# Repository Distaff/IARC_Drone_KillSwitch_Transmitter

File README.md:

# Killswitch for IARC Hat for CMDB
## PCB Design

Board layout:

3D render:

## Usage
- Broadcast killing signal for drones using IARC CMDB hat or other LoRa-based killswitch
- Serve as LoRa packet grabber (by connecting to PC through UART

Board can be powered either from 2x 18650 cells or directly from USB-C (if host provides enough power).
No built-in undervoltage protection circuit is present, except for a warning LED.

## Authors
- Szymon Konopka (PCB Design)
- Piotr Kądziela (schematic design and PCB review)

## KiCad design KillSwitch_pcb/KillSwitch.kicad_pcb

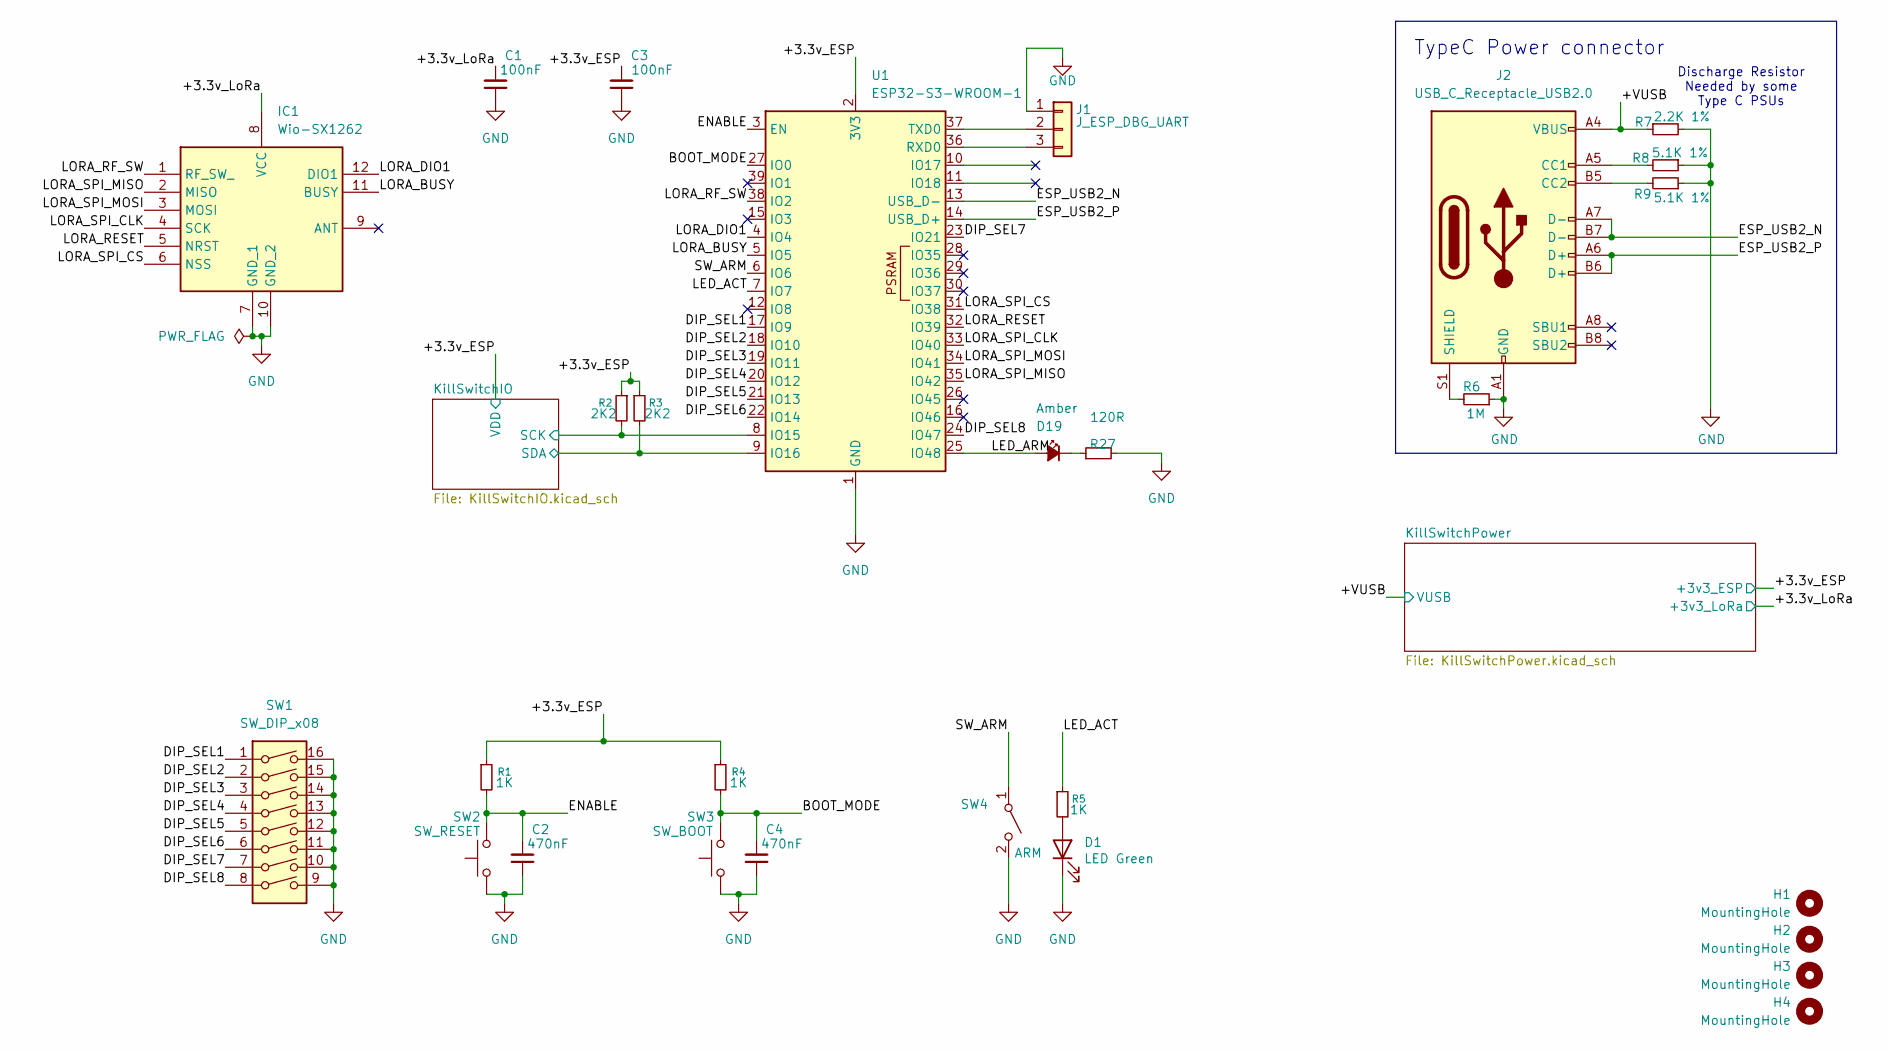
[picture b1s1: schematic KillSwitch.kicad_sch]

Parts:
C1, C3: 100nF; C_0805_2012Metric_Pad1.18x1.45mm_HandSolder
C2, C4: 470nF; C_0805_2012Metric_Pad1.18x1.45mm_HandSolder
D1: LED Green; LED_0603_1608Metric; Part Description Green 572nm LED Indication - Discrete 2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
D19: Amber; LED_Rectangular_W5.0mm_H2.0mm
H1, H2, H3, H4: MountingHole; MountingHole_3.2mm_M3_DIN965
IC1: Wio-SX1262; Mouser Part Number 713-114993390
J1: J_ESP_DBG_UART; Molex_PicoBlade_53047-0310_1x03_P1.25mm_Vertical; Part Description Pin Header, Vertical, Signal, Wire-to-B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
J2: USB_C_Receptacle_USB2.0; USB_C_Receptacle_GCT_USB4105-xx-A_16P_TopMnt_Horizontal; Part Description USBC USB2 data and power connector
R1, R4, R5: 1K; R_0805_2012Metric_Pad1.20x1.40mm_HandSolder
R2, R3: 2K2; R_0805_2012Metric_Pad1.20x1.40mm_HandSolder
R6: 1M; R_0805_2012Metric_Pad1.20x1.40mm_HandSolder; Part Description Resistor 5.1K 1% 63mW
R7: 2.2K 1%; R_0805_2012Metric_Pad1.20x1.40mm_HandSolder; Part Description Resistor 2.2K 1% 63mW
R8, R9: 5.1K 1%; R_0805_2012Metric_Pad1.20x1.40mm_HandSolder; Part Description Resistor 5.1K 1% 63mW
R27: 120R; R_0805_2012Metric_Pad1.20x1.40mm_HandSolder
SW1: SW_DIP_x08; SW_DIP_SPSTx08_Slide_6.7x21.88mm_W8.61mm_P2.54mm_LowProfile
SW2: SW_RESET; SW_Push_1P1T_NO_CK_KMR2; Part Description Tactile Switch, KMR 2 Series, Top Actua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
SW3: SW_BOOT; SW_Push_1P1T_NO_CK_KMR2; Part Description Tactile Switch, KMR 2 Series, Top Actua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
SW4: ARM; SW_Toggle_Blue_wSlots
U1: ESP32-S3-WROOM-1; ESP32-S3-WROOM-1U

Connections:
/+3.3v_ESP: C3.2, R1.1, R2.1, R3.1, R4.1, U1.2 (3V3); also elsewhere on the board
/+3.3v_LoRa: C1.2, IC1.8 (VCC); also elsewhere on the board
/+VUSB: J2.A4 (VBUS), J2.A9 (VBUS), J2.B4 (VBUS), J2.B9 (VBUS), R7.1; also elsewhere on the board
/BOOT_MODE: C4.2, R4.2, SW3.2, U1.27 (IO0)
/DIP_SEL1: SW1.1, U1.17 (IO9)
/DIP_SEL2: SW1.2, U1.18 (IO10)
/DIP_SEL3: SW1.3, U1.19 (IO11)
/DIP_SEL4: SW1.4, U1.20 (IO12)
/DIP_SEL5: SW1.5, U1.21 (IO13)
/DIP_SEL6: SW1.6, U1.22 (IO14)
/DIP_SEL7: SW1.7, U1.23 (IO21)
/DIP_SEL8: SW1.8, U1.24 (IO47)
/ENABLE: C2.2, R1.2, SW2.2, U1.3 (EN)
/ESP_USB2_N: J2.A7 (D-), J2.B7 (D-), U1.13 (USB_D-)
/ESP_USB2_P: J2.A6 (D+), J2.B6 (D+), U1.14 (USB_D+)
/KillSwitchIO/SCK: R2.2, U1.8 (IO15); also elsewhere on the board
/KillSwitchIO/SDA: R3.2, U1.9 (IO16); also elsewhere on the board
/LED_ACT: R5.1, U1.7 (IO7)
/LED_ARM: D19.2 (A), U1.25 (IO48)
/LORA_BUSY: IC1.11 (BUSY), U1.5 (IO5)
/LORA_DIO1: IC1.12 (DIO1), U1.4 (IO4)
/LORA_RESET: IC1.5 (NRST), U1.32 (IO39)
/LORA_RF_SW: IC1.1 (RF_SW_), U1.38 (IO2)
/LORA_SPI_CLK: IC1.4 (SCK), U1.33 (IO40)
/LORA_SPI_CS: IC1.6 (NSS), U1.31 (IO38)
/LORA_SPI_MISO: IC1.2 (MISO), U1.35 (IO42)
/LORA_SPI_MOSI: IC1.3 (MOSI), U1.34 (IO41)
/SW_ARM: SW4.1 (A), U1.6 (IO6)
GND: C1.1, C2.1, C3.1, C4.1, D1.1 (K), IC1.7 (GND_1), IC1.10 (GND_2), J1.1, J2.A1 (GND), J2.A12 (GND), J2.B1 (GND), J2.B12 (GND), R6.1, R7.2, R8.1, R9.1, R27.2, SW1.9, SW1.10, SW1.11, SW1.12, SW1.13, SW1.14, SW1.15, SW1.16, SW2.1, SW3.1, SW4.2 (B), U1.1 (GND), U1.40 (GND), U1.41 (GND); also elsewhere on the board
unnamed: D1.2 (A), R5.2
unnamed: D19.1 (K), R27.1
unnamed: J1.2, U1.37 (TXD0)
unnamed: J1.3, U1.36 (RXD0)
unnamed: J2.A5 (CC1), R8.2
unnamed: J2.B5 (CC2), R9.2
unnamed: J2.S1 (SHIELD), R6.2

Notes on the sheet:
Discharge Resistor Needed by some Type C PSUs
TypeC Power connector

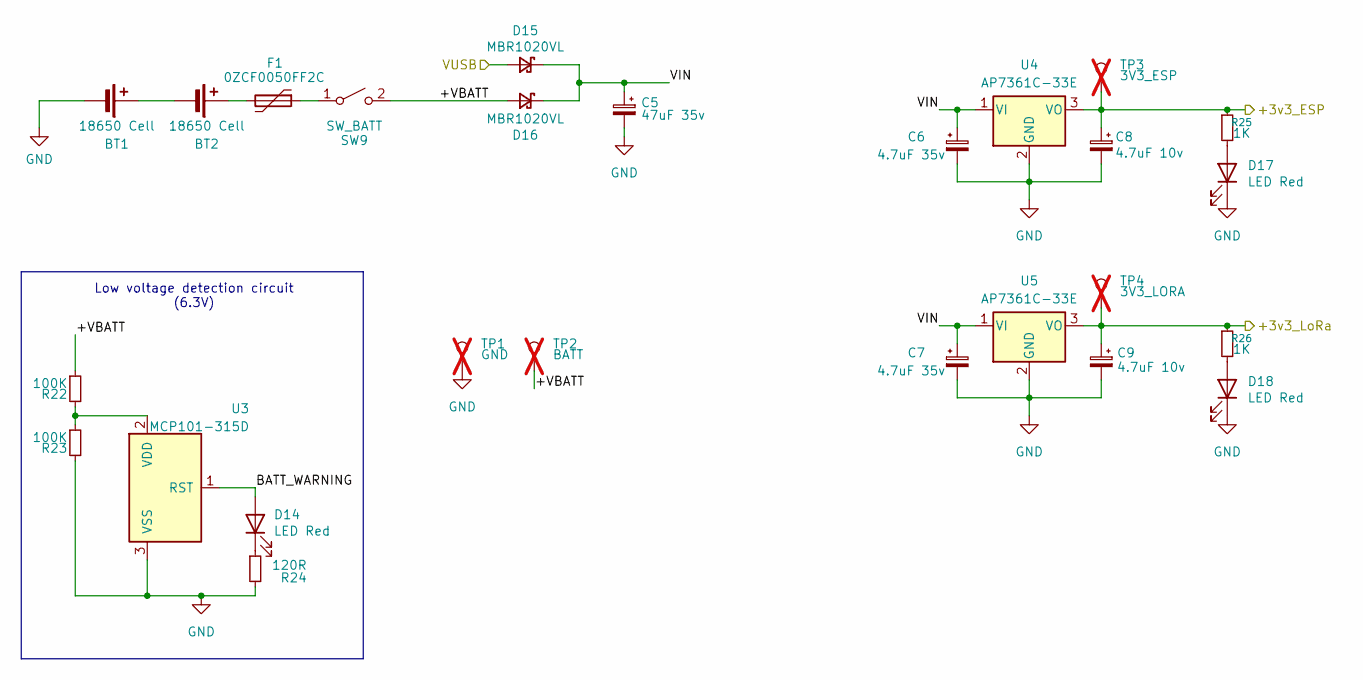
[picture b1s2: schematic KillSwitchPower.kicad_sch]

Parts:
BT1, BT2: 18650 Cell; BAT_BH-18650-PC
C5: 47uF 35v; CP_EIA-7343-31_Kemet-D_HandSolder
C6, C7: 4.7uF 35v; CP_EIA-3528-21_Kemet-B_HandSolder
C8, C9: 4.7uF 10v; CP_EIA-3216-18_Kemet-A_HandSolder
D14, D17, D18: LED Red; LED_0603_1608Metric; Part Description Red 620nm LED Indication - Discrete 2.2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
D15, D16: MBR1020VL; D_SOD-123F
F1: 0ZCF0050FF2C; Fuse_2920_7451Metric_Pad2.10x5.45mm_HandSolder
R22, R23: 100K; R_0805_2012Metric_Pad1.20x1.40mm_HandSolder
R24: 120R; R_Axial_DIN0204_L3.6mm_D1.6mm_P2.54mm_Vertical
R25, R26: 1K; R_0805_2012Metric_Pad1.20x1.40mm_HandSolder
SW9: SW_BATT; SL19121
TP1: GND; TestPoint_Pad_2.0x2.0mm; Part Description Test point; not fitted
TP2: BATT; TestPoint_Pad_2.0x2.0mm; Part Description Test point; not fitted
TP3: 3V3_ESP; TestPoint_Pad_2.0x2.0mm; Part Description Test point; not fitted
TP4: 3V3_LORA; TestPoint_Pad_2.0x2.0mm; Part Description Test point; not fitted
U3: MCP101-315D; SOT-23-3
U4, U5: AP7361C-33E; SOT-223-3_TabPin2; Part Description LDO, FIXED, 3.3V, 1A, -40 TO 85DEG C

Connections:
/+3.3v_ESP: C8.1, R25.1, TP3.1, U4.3 (VO); also elsewhere on the board
/+3.3v_LoRa: C9.1, R26.1, TP4.1, U5.3 (VO); also elsewhere on the board
/+VUSB: D15.2 (A); also elsewhere on the board
/KillSwitchPower/+VBATT: D16.2 (A), R22.1, SW9.2 (B), TP2.1
/KillSwitchPower/BATT_WARNING: D14.2 (A), U3.1 (RST)
/KillSwitchPower/VIN: C5.1, C6.1, C7.1, D15.1 (K), D16.1 (K), U4.1 (VI), U5.1 (VI)
GND: BT1.2 (-), C5.2, C6.2, C7.2, C8.2, C9.2, D17.1 (K), D18.1 (K), R23.2, R24.2, TP1.1, U3.3 (VSS), U4.2 (GND), U5.2 (GND); also elsewhere on the board
unnamed: BT1.1 (+), BT2.2 (-)
unnamed: BT2.1 (+), F1.2
unnamed: D14.1 (K), R24.1
unnamed: D17.2 (A), R25.2
unnamed: D18.2 (A), R26.2
unnamed: F1.1, SW9.1 (A)
unnamed: R22.2, R23.1, U3.2 (VDD)

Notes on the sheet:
Low voltage detection circuit (6.3V)

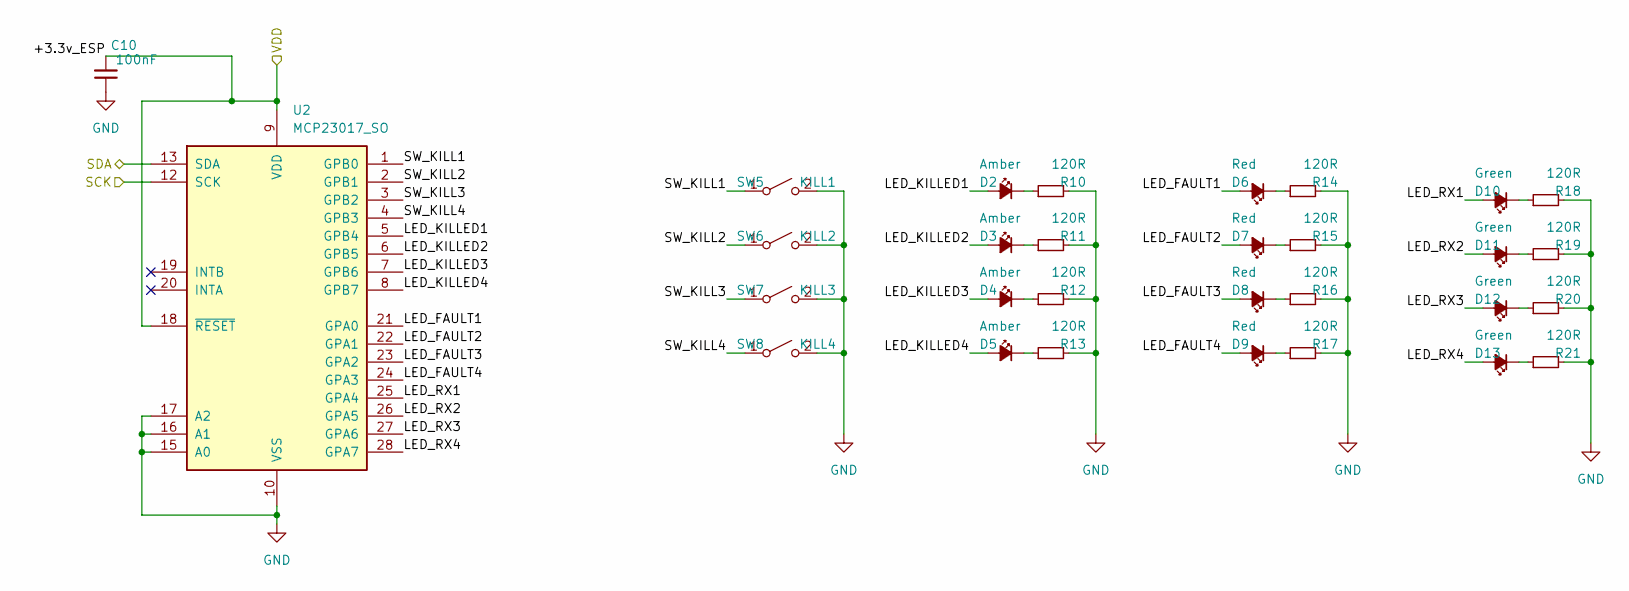
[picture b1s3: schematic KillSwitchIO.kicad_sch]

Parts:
C10: 100nF; C_0805_2012Metric_Pad1.18x1.45mm_HandSolder
D2, D3, D4, D5: Amber; LED_Rectangular_W5.0mm_H2.0mm
D6, D7, D8, D9: Red; LED_Rectangular_W5.0mm_H2.0mm
D10, D11, D12, D13: Green; LED_Rectangular_W5.0mm_H2.0mm
R10, R11, R12, R13, R14, R15, R16, R17, R18, R19, R20, R21: 120R; R_0805_2012Metric_Pad1.20x1.40mm_HandSolder
SW5: KILL1; SW_Toggle_Blue_wSlots
SW6: KILL2; SW_Toggle_Blue_wSlots
SW7: KILL3; SW_Toggle_Blue_wSlots
SW8: KILL4; SW_Toggle_Blue_wSlots
U2: MCP23017_SO; SOIC-28W_7.5x17.9mm_P1.27mm

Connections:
/+3.3v_ESP: C10.2, U2.9 (VDD), U2.18 (~RESET); also elsewhere on the board
/KillSwitchIO/LED_FAULT1: D6.2 (A), U2.21 (GPA0)
/KillSwitchIO/LED_FAULT2: D7.2 (A), U2.22 (GPA1)
/KillSwitchIO/LED_FAULT3: D8.2 (A), U2.23 (GPA2)
/KillSwitchIO/LED_FAULT4: D9.2 (A), U2.24 (GPA3)
/KillSwitchIO/LED_KILLED1: D2.2 (A), U2.5 (GPB4)
/KillSwitchIO/LED_KILLED2: D3.2 (A), U2.6 (GPB5)
/KillSwitchIO/LED_KILLED3: D4.2 (A), U2.7 (GPB6)
/KillSwitchIO/LED_KILLED4: D5.2 (A), U2.8 (GPB7)
/KillSwitchIO/LED_RX1: D10.2 (A), U2.25 (GPA4)
/KillSwitchIO/LED_RX2: D11.2 (A), U2.26 (GPA5)
/KillSwitchIO/LED_RX3: D12.2 (A), U2.27 (GPA6)
/KillSwitchIO/LED_RX4: D13.2 (A), U2.28 (GPA7)
/KillSwitchIO/SCK: U2.12 (SCK); also elsewhere on the board
/KillSwitchIO/SDA: U2.13 (SDA); also elsewhere on the board
/KillSwitchIO/SW_KILL1: SW5.1 (A), U2.1 (GPB0)
/KillSwitchIO/SW_KILL2: SW6.1 (A), U2.2 (GPB1)
/KillSwitchIO/SW_KILL3: SW7.1 (A), U2.3 (GPB2)
/KillSwitchIO/SW_KILL4: SW8.1 (A), U2.4 (GPB3)
GND: C10.1, R10.2, R11.2, R12.2, R13.2, R14.2, R15.2, R16.2, R17.2, R18.2, R19.2, R20.2, R21.2, SW5.2 (B), SW6.2 (B), SW7.2 (B), SW8.2 (B), U2.10 (VSS), U2.15 (A0), U2.16 (A1), U2.17 (A2); also elsewhere on the board
unnamed: D2.1 (K), R10.1
unnamed: D3.1 (K), R11.1
unnamed: D4.1 (K), R12.1
unnamed: D5.1 (K), R13.1
unnamed: D6.1 (K), R14.1
unnamed: D7.1 (K), R15.1
unnamed: D8.1 (K), R16.1
unnamed: D9.1 (K), R17.1
unnamed: D10.1 (K), R18.1
unnamed: D11.1 (K), R19.1
unnamed: D12.1 (K), R20.1
unnamed: D13.1 (K), R21.1

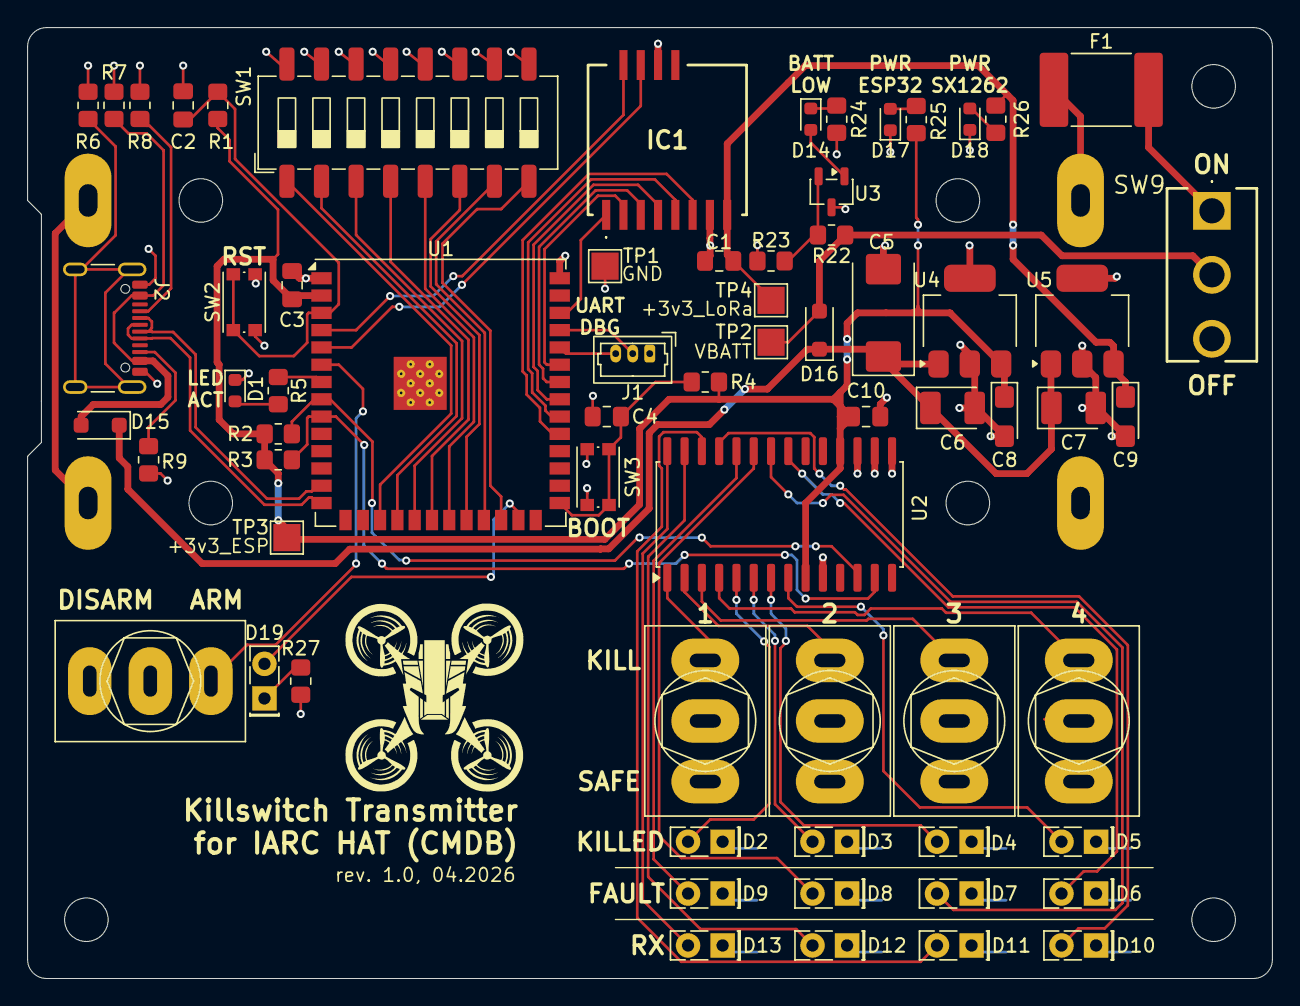
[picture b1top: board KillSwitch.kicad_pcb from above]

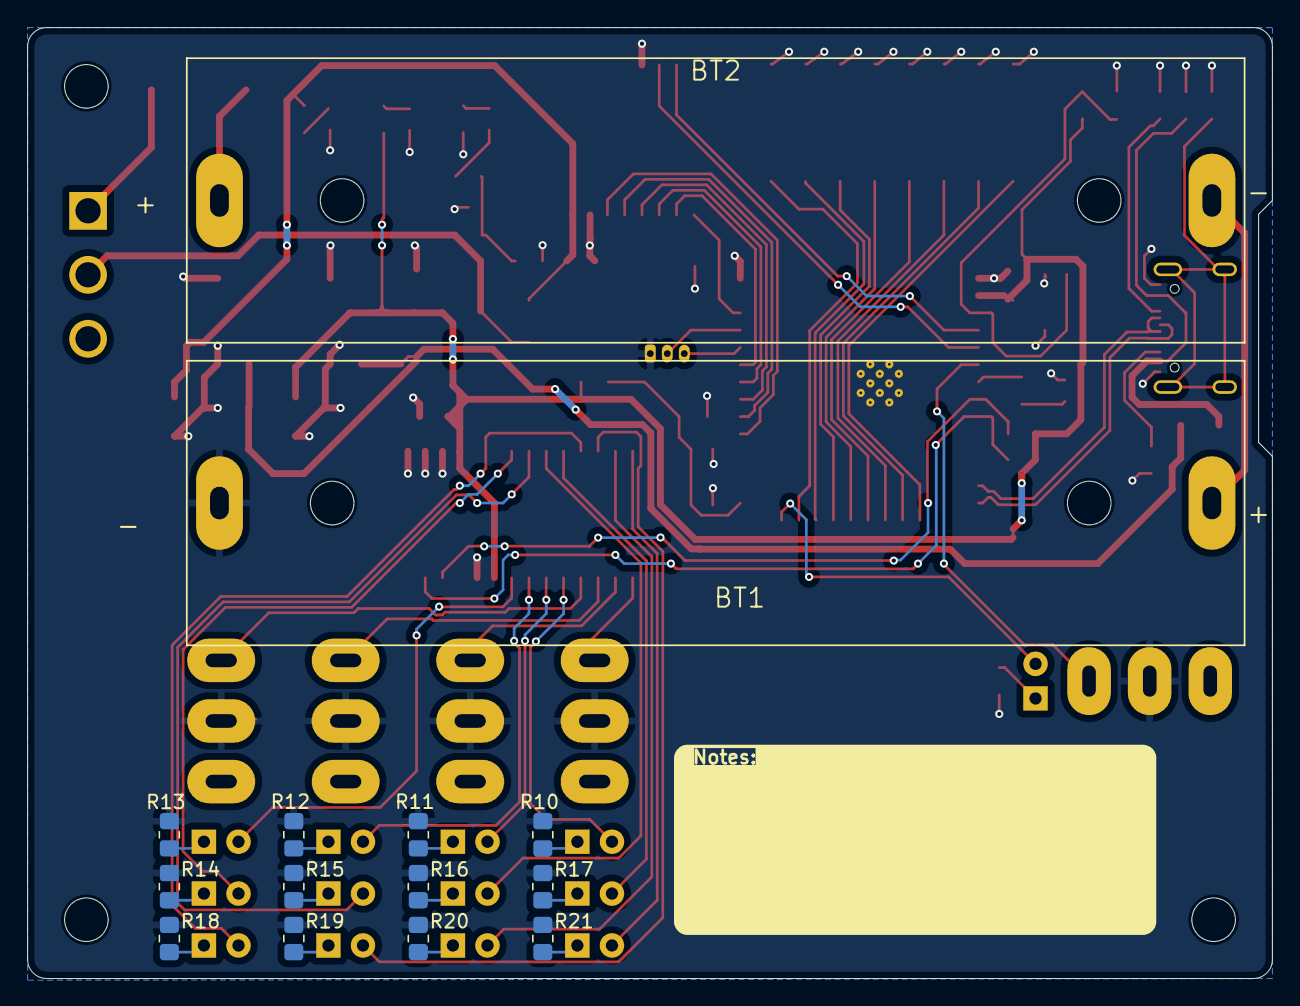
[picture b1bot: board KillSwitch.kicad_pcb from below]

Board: 2 copper layers, 91.4 x 69.8 mm, 83 parts (14 on the bottom side), 74 nets.

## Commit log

2026-04-15 move files into pcb directory
2026-04-15 add pullups for i2c, reannotate, update footprints
2026-04-23 update płytki: Routing bez GND plus obrys bez zaokrągleń i przycięć
2026-04-28 końcowa werjsa
2026-04-29 Move LEDs resistors to the back side, correct decoupling caps, add aesthetic changes
